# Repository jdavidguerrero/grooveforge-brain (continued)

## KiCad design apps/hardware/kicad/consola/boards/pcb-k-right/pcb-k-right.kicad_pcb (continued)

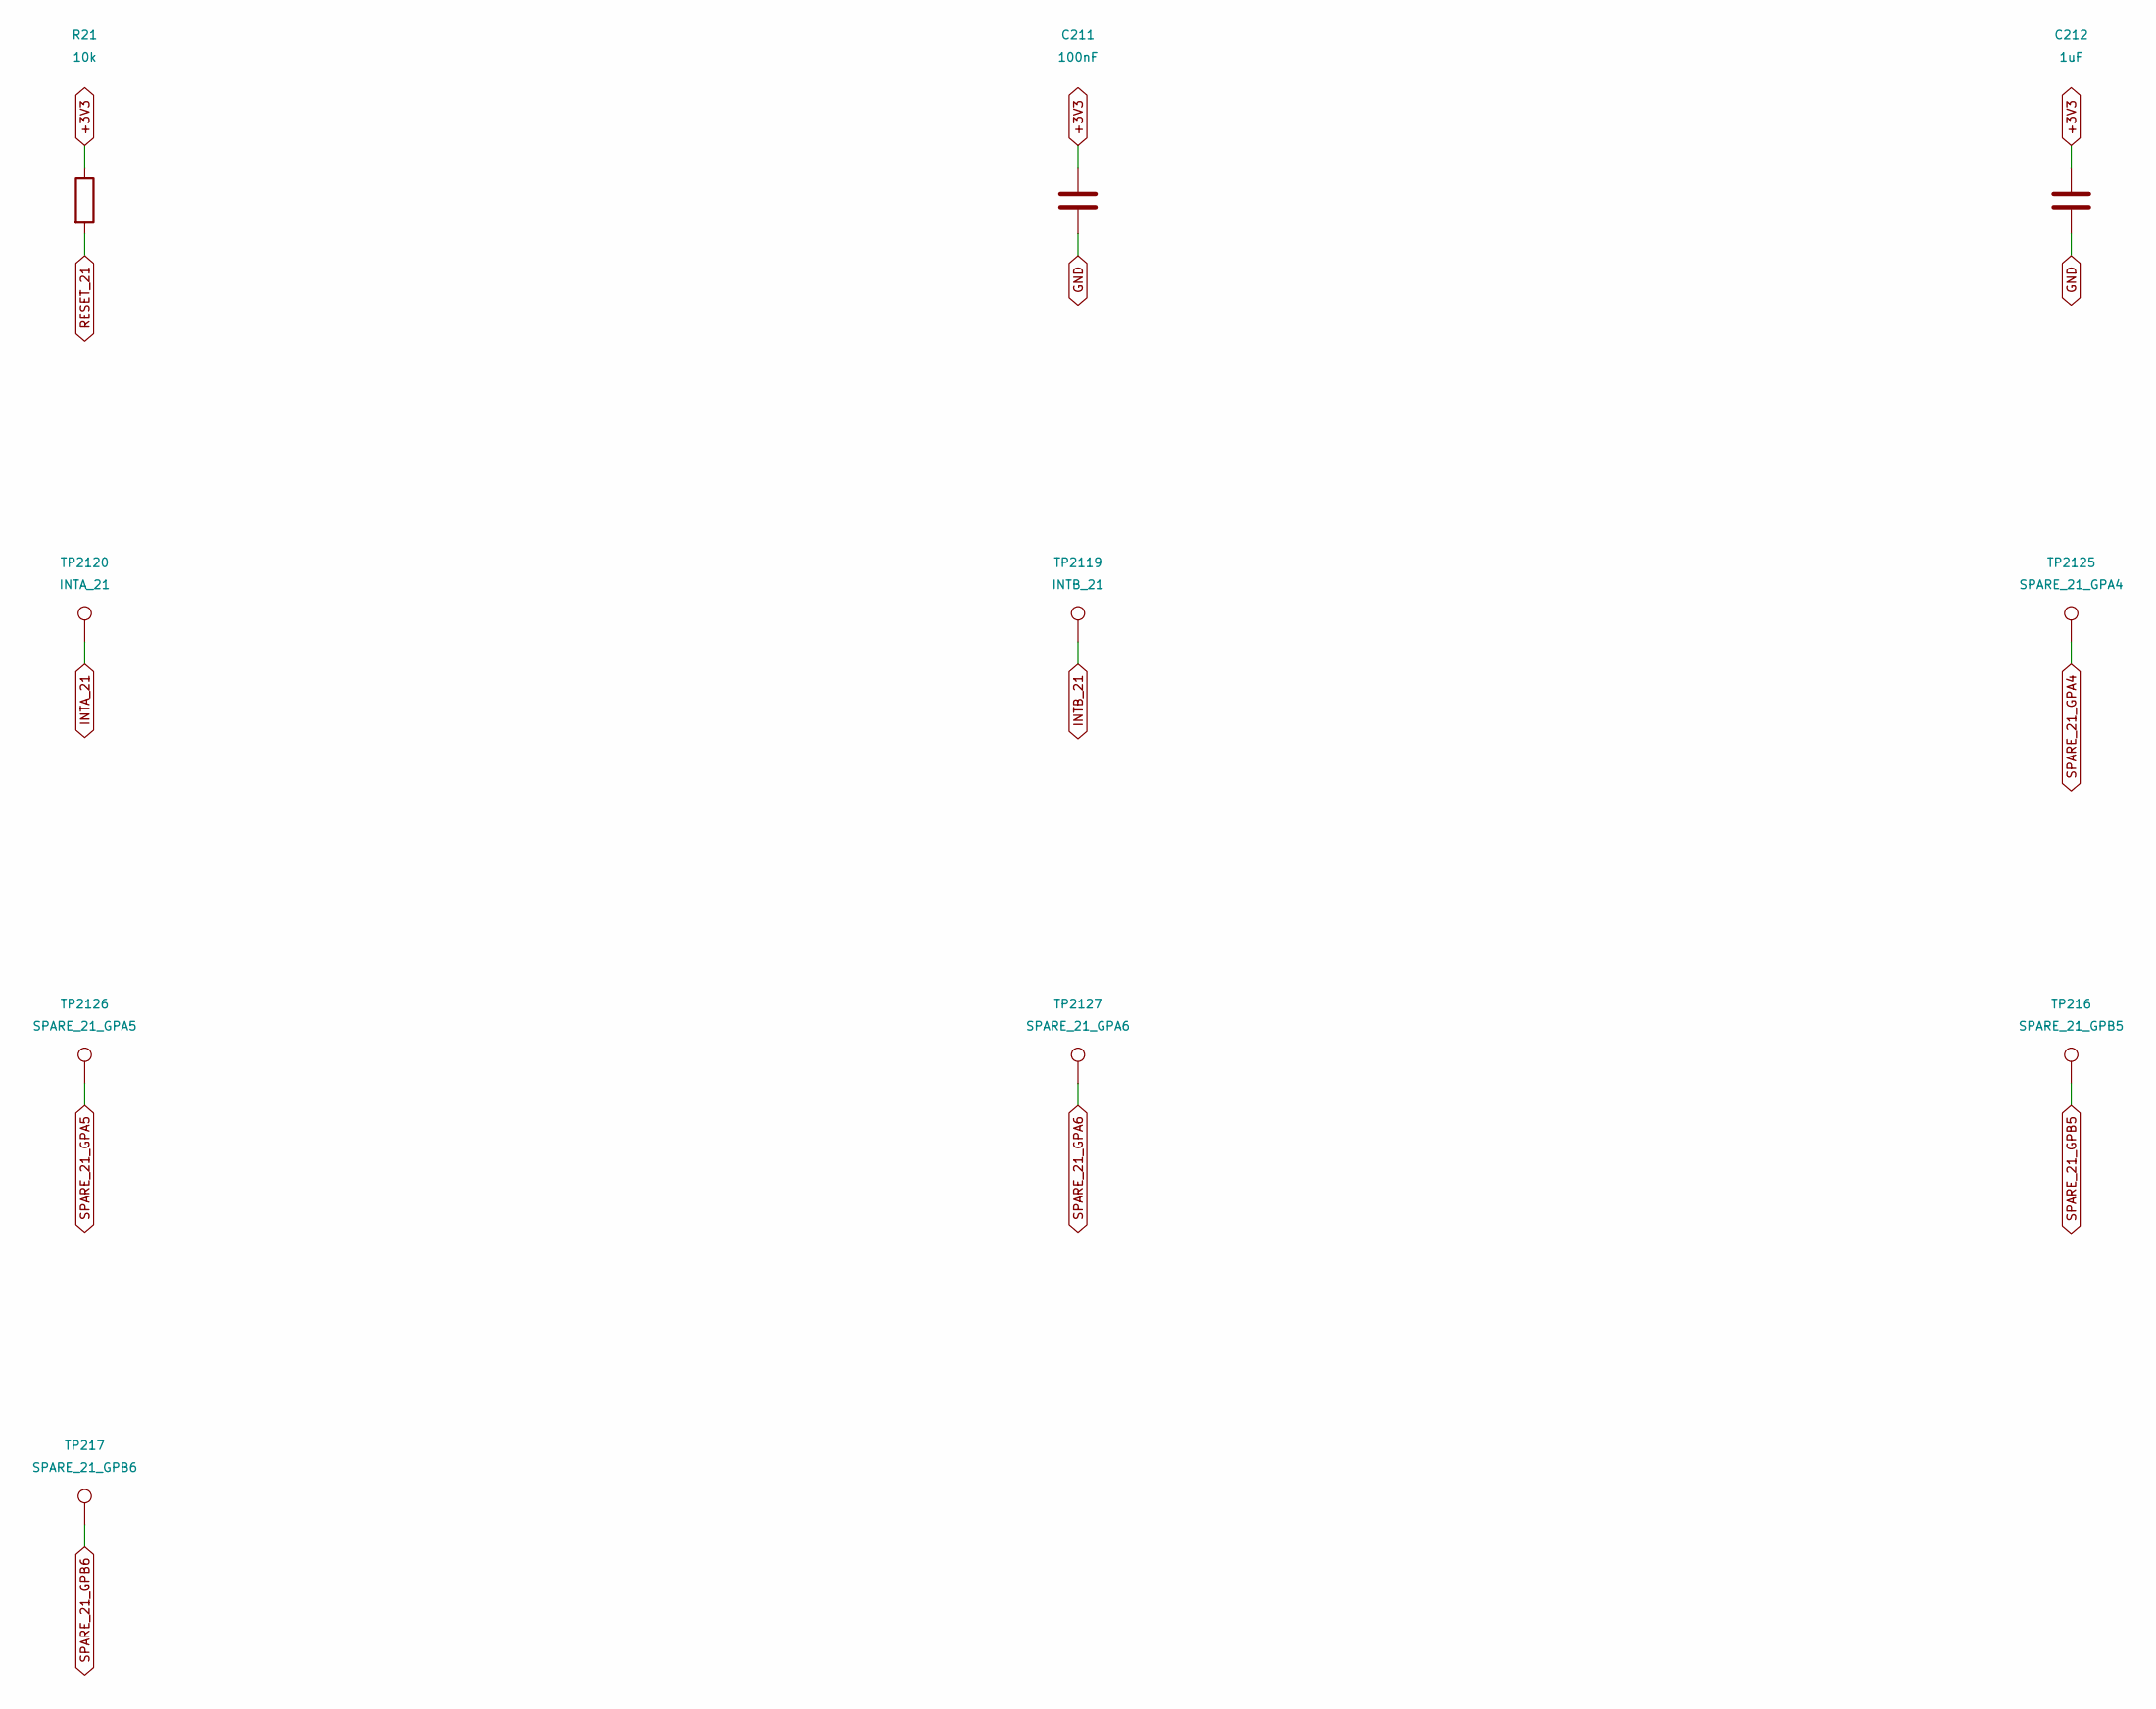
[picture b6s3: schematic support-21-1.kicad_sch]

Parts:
C211: 100nF; C_0805_2012Metric; MPN CC0805KRX7R9BB104; LCSC C49678
C212: 1uF; C_0805_2012Metric; MPN FCC0805B105K500FT; LCSC C5137478
R21: 10k; R_0805_2012Metric; MPN 0805W8F1002T5E; LCSC C17414
TP216: SPARE_21_GPB5; TestPoint_Pad_D1.5mm
TP217: SPARE_21_GPB6; TestPoint_Pad_D1.5mm
TP2119: INTB_21; TestPoint_Pad_D1.5mm
TP2120: INTA_21; TestPoint_Pad_D1.5mm
TP2125: SPARE_21_GPA4; TestPoint_Pad_D1.5mm
TP2126: SPARE_21_GPA5; TestPoint_Pad_D1.5mm
TP2127: SPARE_21_GPA6; TestPoint_Pad_D1.5mm

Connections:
+3V3: C211.1, C212.1, R21.1; also elsewhere on the board
GND: C211.2, C212.2; also elsewhere on the board
INTA_21: TP2120.1; also elsewhere on the board
INTB_21: TP2119.1; also elsewhere on the board
RESET_21: R21.2; also elsewhere on the board
SPARE_21_GPA4: TP2125.1; also elsewhere on the board
SPARE_21_GPA5: TP2126.1; also elsewhere on the board
SPARE_21_GPA6: TP2127.1; also elsewhere on the board
SPARE_21_GPB5: TP216.1; also elsewhere on the board
SPARE_21_GPB6: TP217.1; also elsewhere on the board

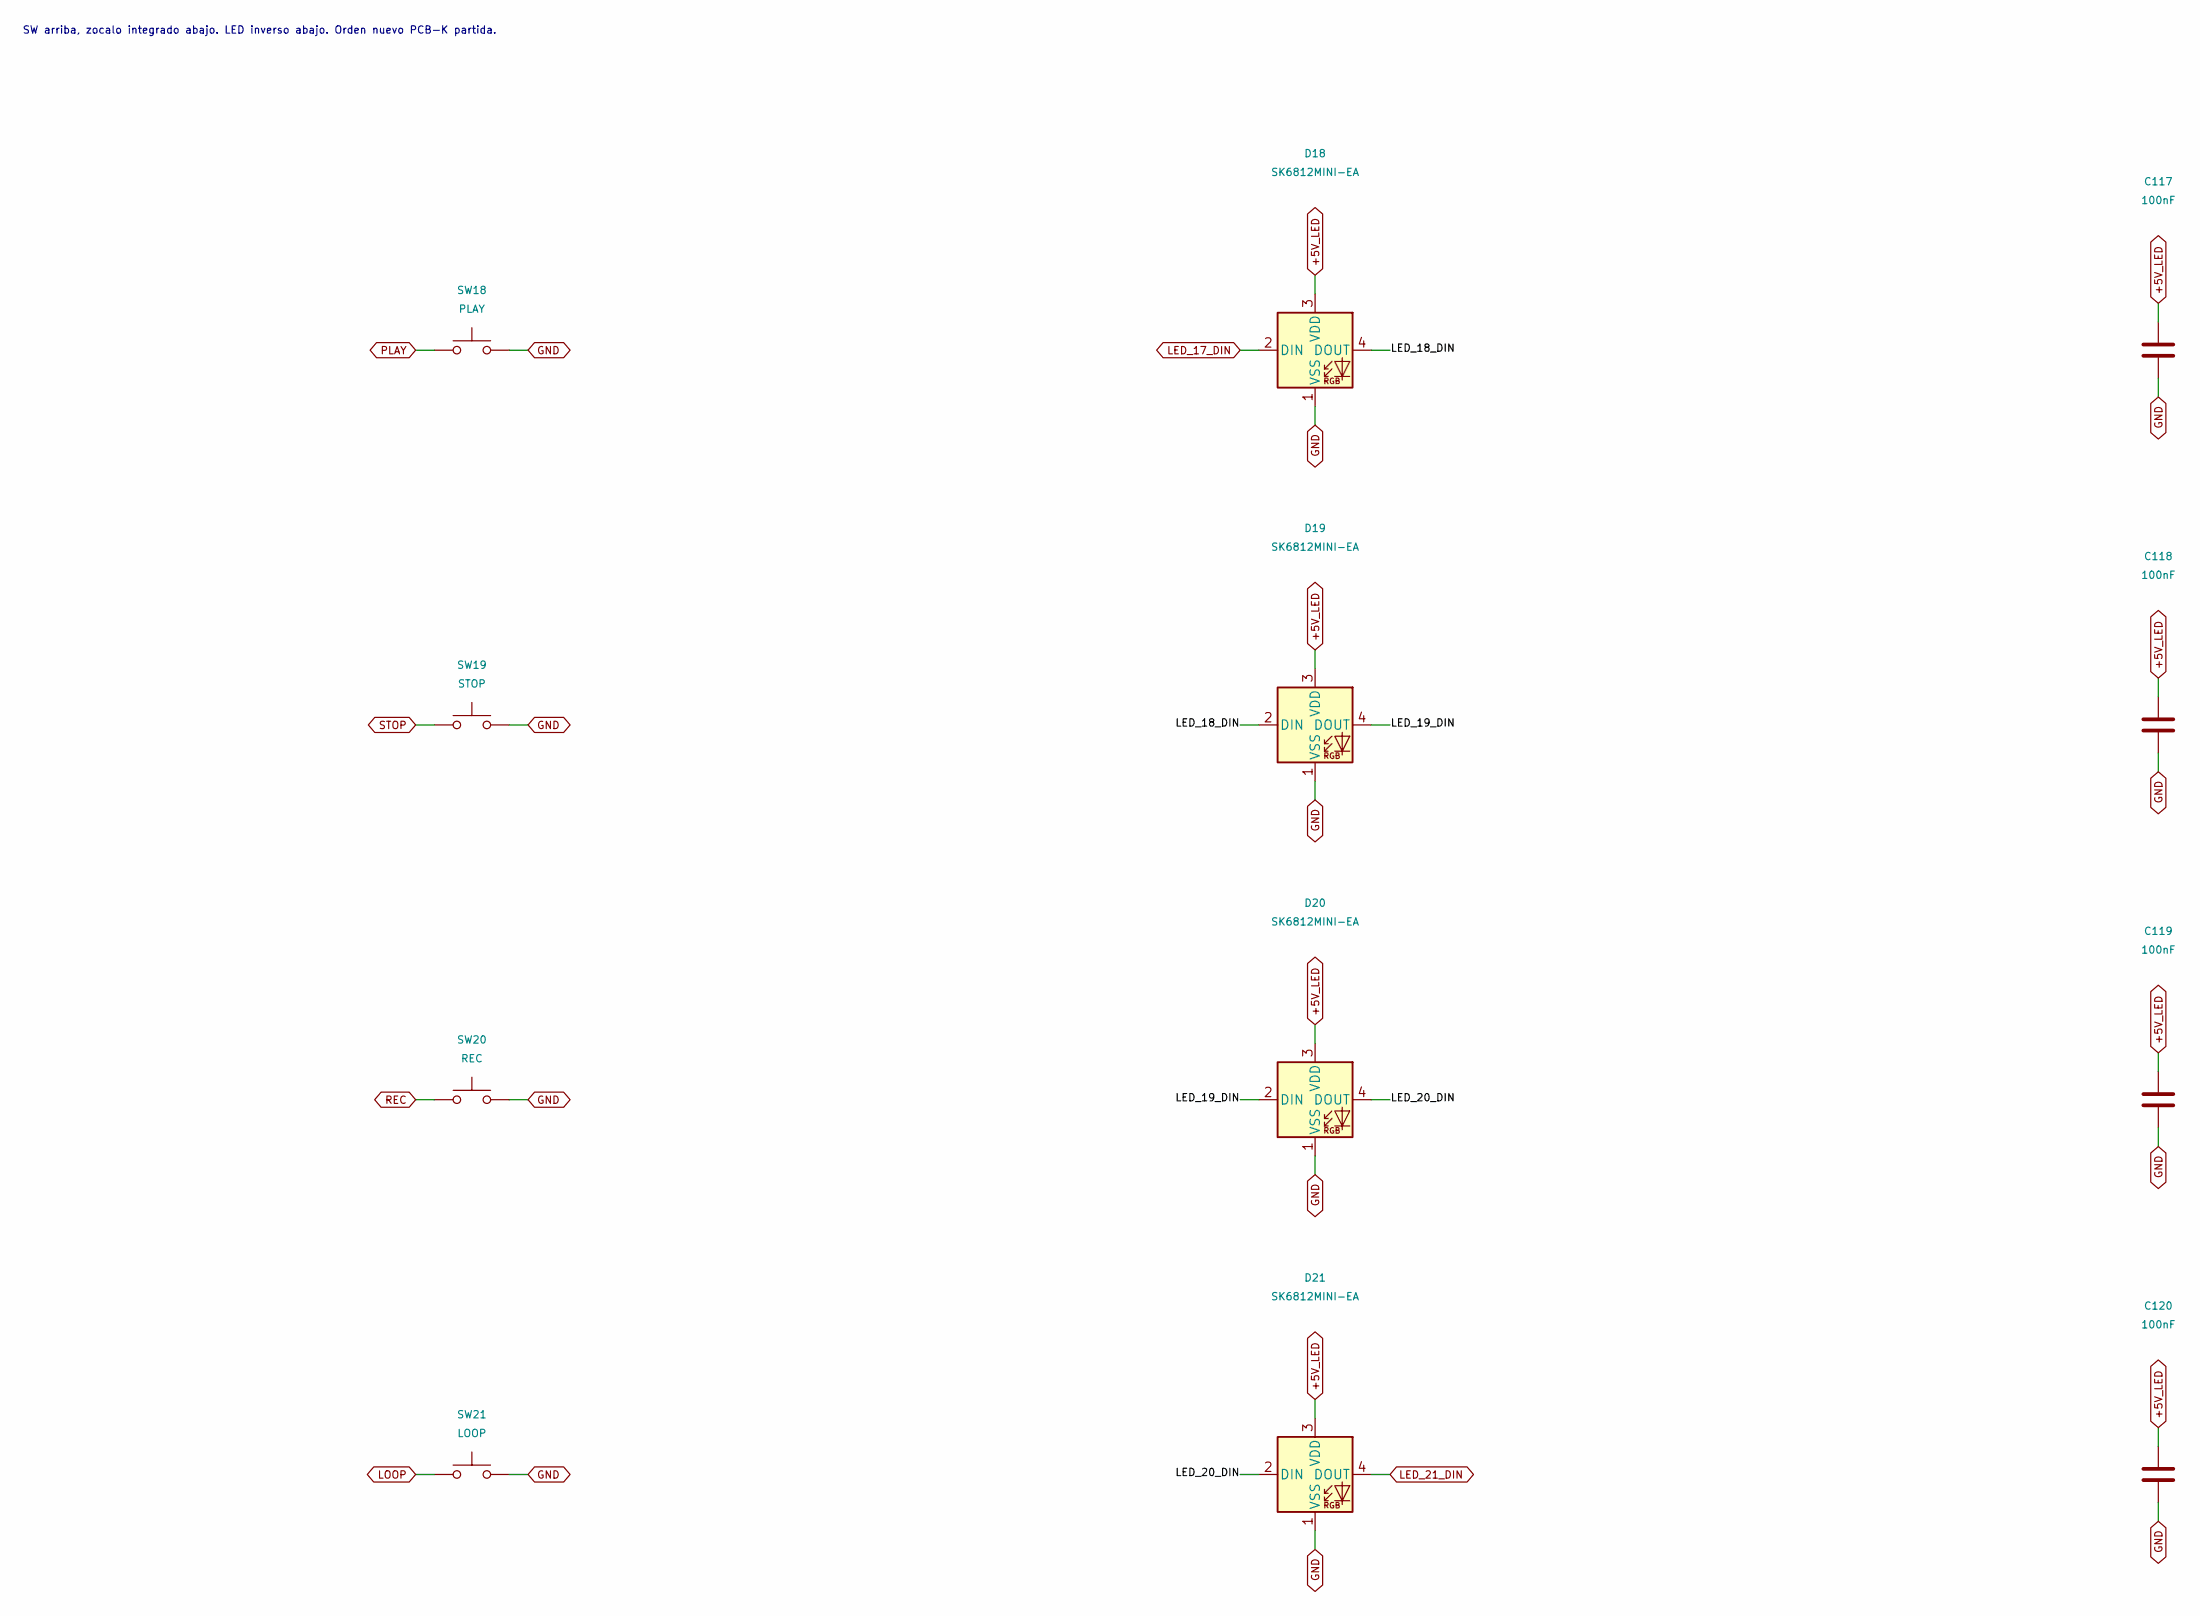
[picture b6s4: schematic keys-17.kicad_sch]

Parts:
C117, C118, C119, C120: 100nF; C_0805_2012Metric; MPN CC0805KRX7R9BB104; LCSC C49678
D18, D19, D20, D21: SK6812MINI-EA; SK6812MINI-EA_ReverseMount; MPN SK6812MINI-EA; LCSC C5378731
SW18: PLAY; Kailh_Choc_V2_PG1353_Hotswap
SW19: STOP; Kailh_Choc_V2_PG1353_Hotswap
SW20: REC; Kailh_Choc_V2_PG1353_Hotswap
SW21: LOOP; Kailh_Choc_V2_PG1353_Hotswap

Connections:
+5V_LED: C117.1, C118.1, C119.1, C120.1, D18.3 (VDD), D19.3 (VDD), D20.3 (VDD), D21.3 (VDD); also elsewhere on the board
/keys-17/LED_18_DIN: D18.4 (DOUT), D19.2 (DIN)
/keys-17/LED_19_DIN: D19.4 (DOUT), D20.2 (DIN)
/keys-17/LED_20_DIN: D20.4 (DOUT), D21.2 (DIN)
GND: C117.2, C118.2, C119.2, C120.2, D18.1 (VSS), D19.1 (VSS), D20.1 (VSS), D21.1 (VSS), SW18.2, SW19.2, SW20.2, SW21.2; also elsewhere on the board
LED_17_DIN: D18.2 (DIN); also elsewhere on the board
LED_21_DIN: D21.4 (DOUT); also elsewhere on the board
LOOP: SW21.1; also elsewhere on the board
PLAY: SW18.1; also elsewhere on the board
REC: SW20.1; also elsewhere on the board
STOP: SW19.1; also elsewhere on the board

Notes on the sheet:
SW arriba, zocalo integrado abajo. LED inverso abajo. Orden nuevo PCB-K partida.

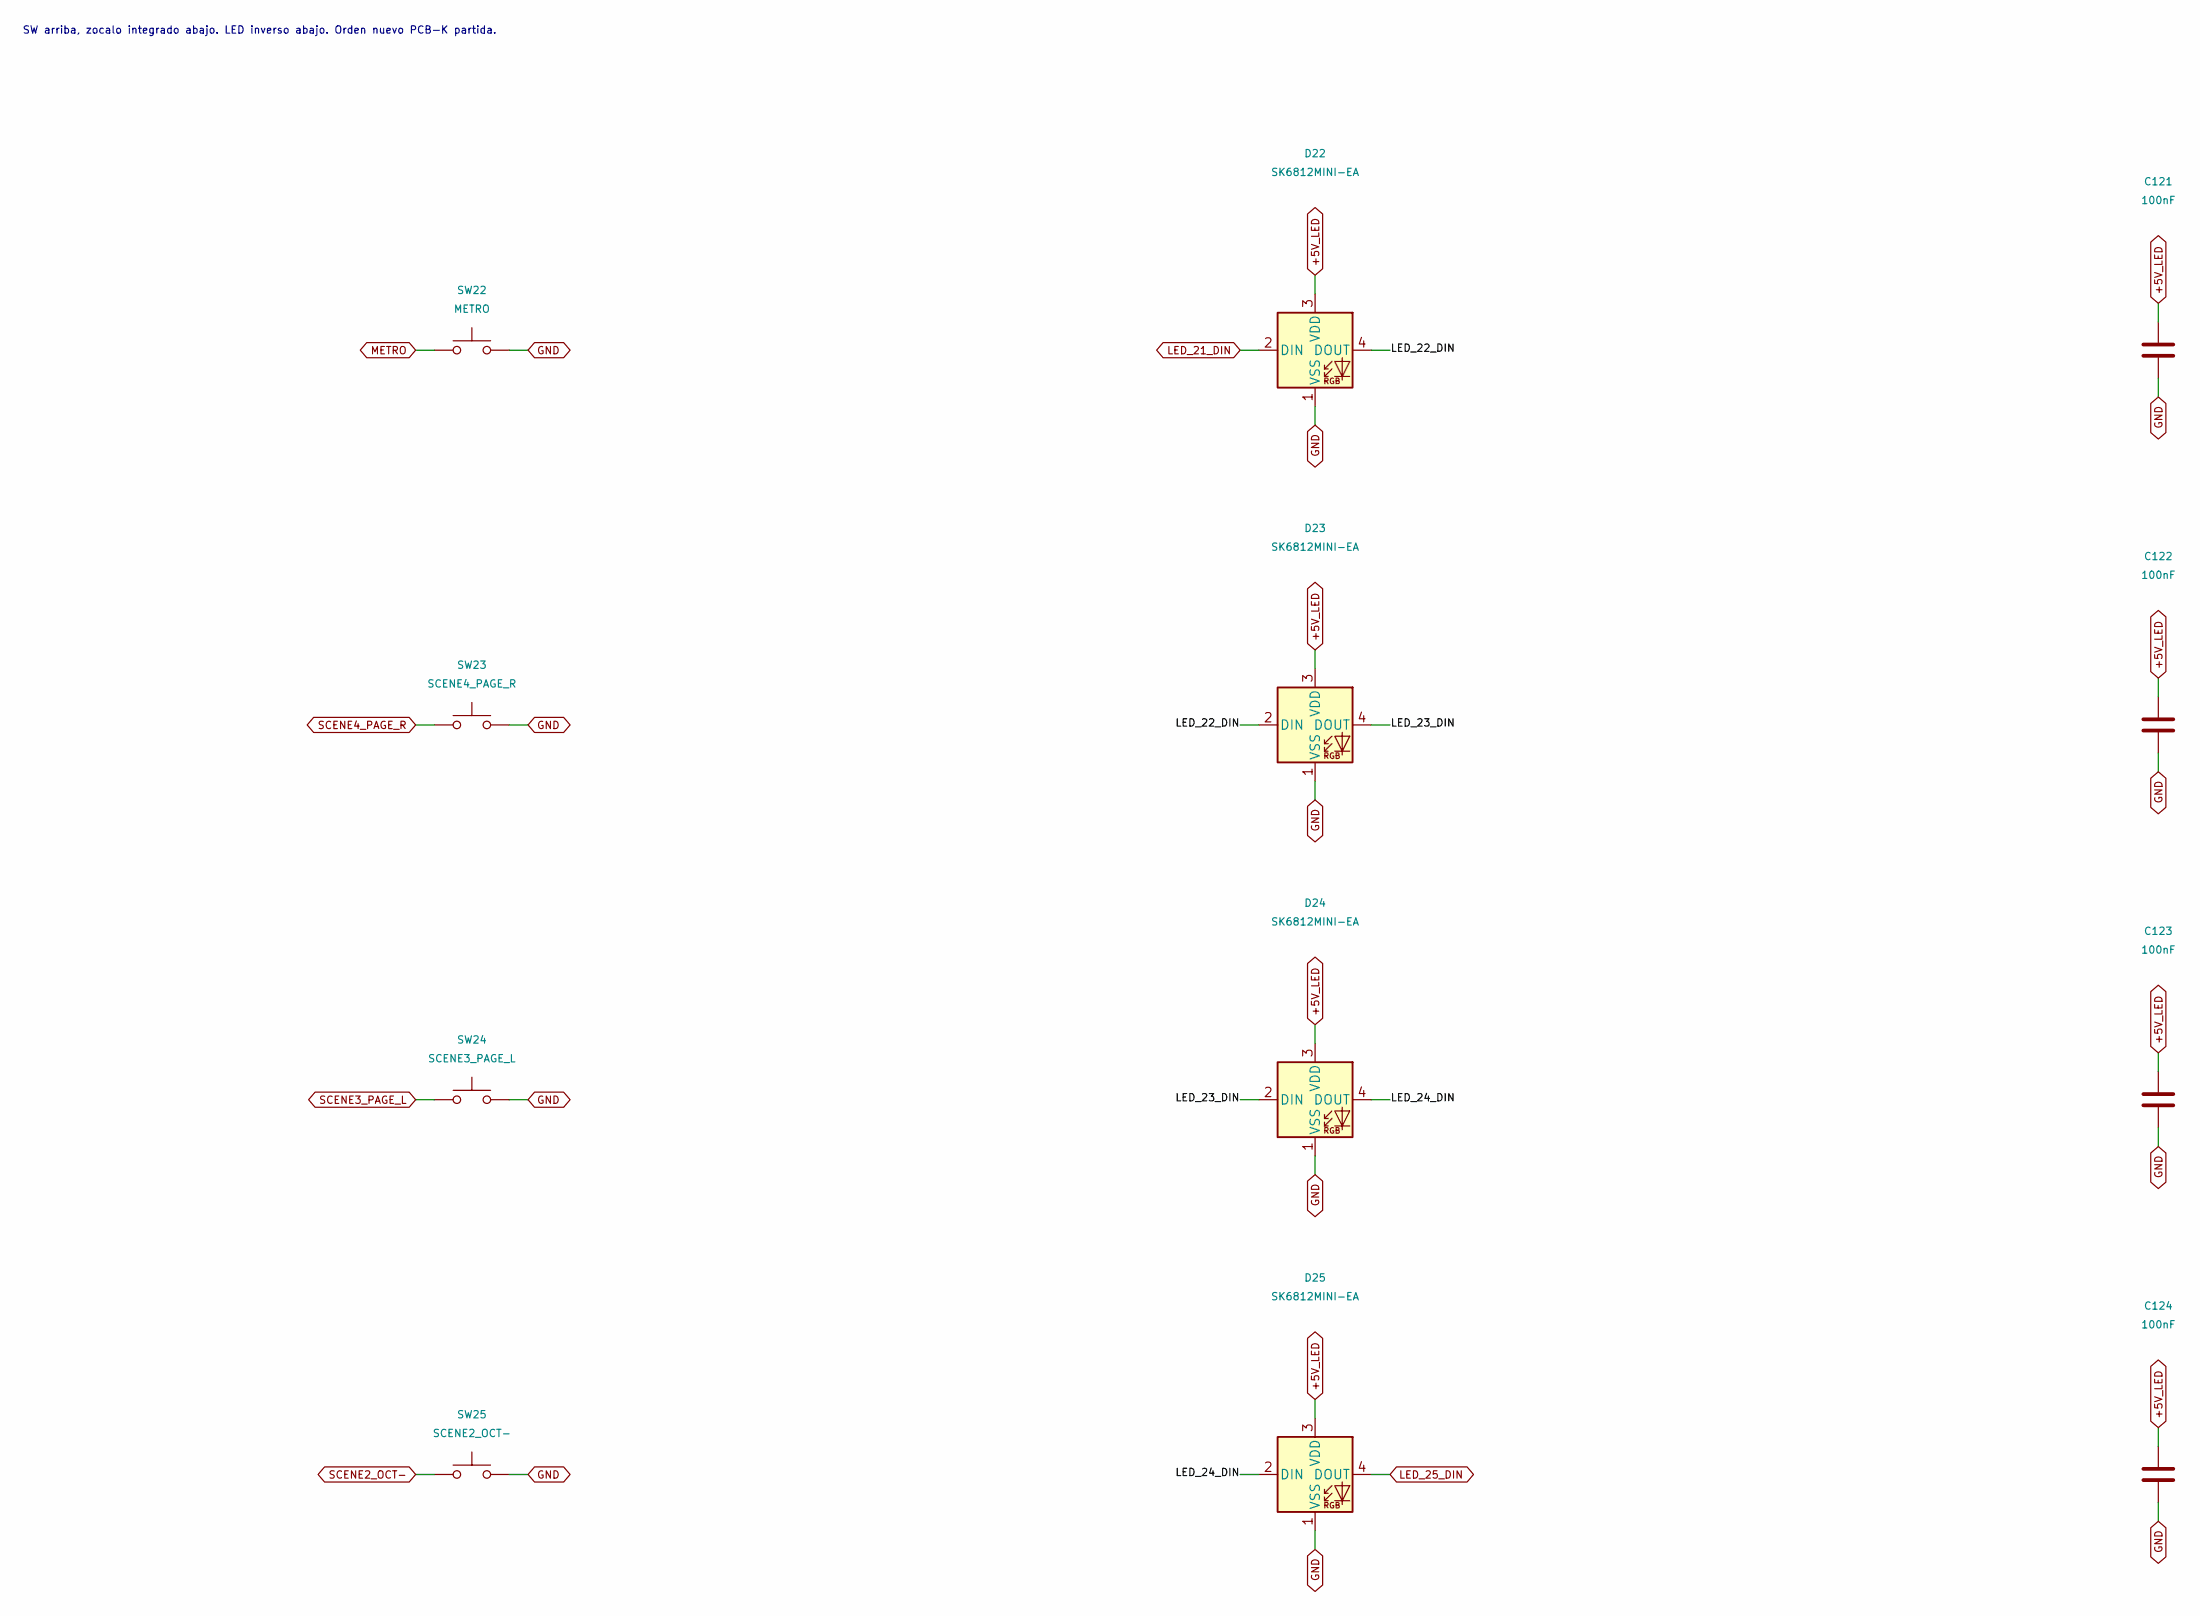
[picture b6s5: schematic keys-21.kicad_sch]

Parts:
C121, C122, C123, C124: 100nF; C_0805_2012Metric; MPN CC0805KRX7R9BB104; LCSC C49678
D22, D23, D24, D25: SK6812MINI-EA; SK6812MINI-EA_ReverseMount; MPN SK6812MINI-EA; LCSC C5378731
SW22: METRO; Kailh_Choc_V2_PG1353_Hotswap
SW23: SCENE4_PAGE_R; Kailh_Choc_V2_PG1353_Hotswap
SW24: SCENE3_PAGE_L; Kailh_Choc_V2_PG1353_Hotswap
SW25: SCENE2_OCT-; Kailh_Choc_V2_PG1353_Hotswap

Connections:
+5V_LED: C121.1, C122.1, C123.1, C124.1, D22.3 (VDD), D23.3 (VDD), D24.3 (VDD), D25.3 (VDD); also elsewhere on the board
/keys-21/LED_22_DIN: D22.4 (DOUT), D23.2 (DIN)
/keys-21/LED_23_DIN: D23.4 (DOUT), D24.2 (DIN)
/keys-21/LED_24_DIN: D24.4 (DOUT), D25.2 (DIN)
GND: C121.2, C122.2, C123.2, C124.2, D22.1 (VSS), D23.1 (VSS), D24.1 (VSS), D25.1 (VSS), SW22.2, SW23.2, SW24.2, SW25.2; also elsewhere on the board
LED_21_DIN: D22.2 (DIN); also elsewhere on the board
LED_25_DIN: D25.4 (DOUT); also elsewhere on the board
METRO: SW22.1; also elsewhere on the board
SCENE2_OCT-: SW25.1; also elsewhere on the board
SCENE3_PAGE_L: SW24.1; also elsewhere on the board
SCENE4_PAGE_R: SW23.1; also elsewhere on the board

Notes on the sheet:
SW arriba, zocalo integrado abajo. LED inverso abajo. Orden nuevo PCB-K partida.

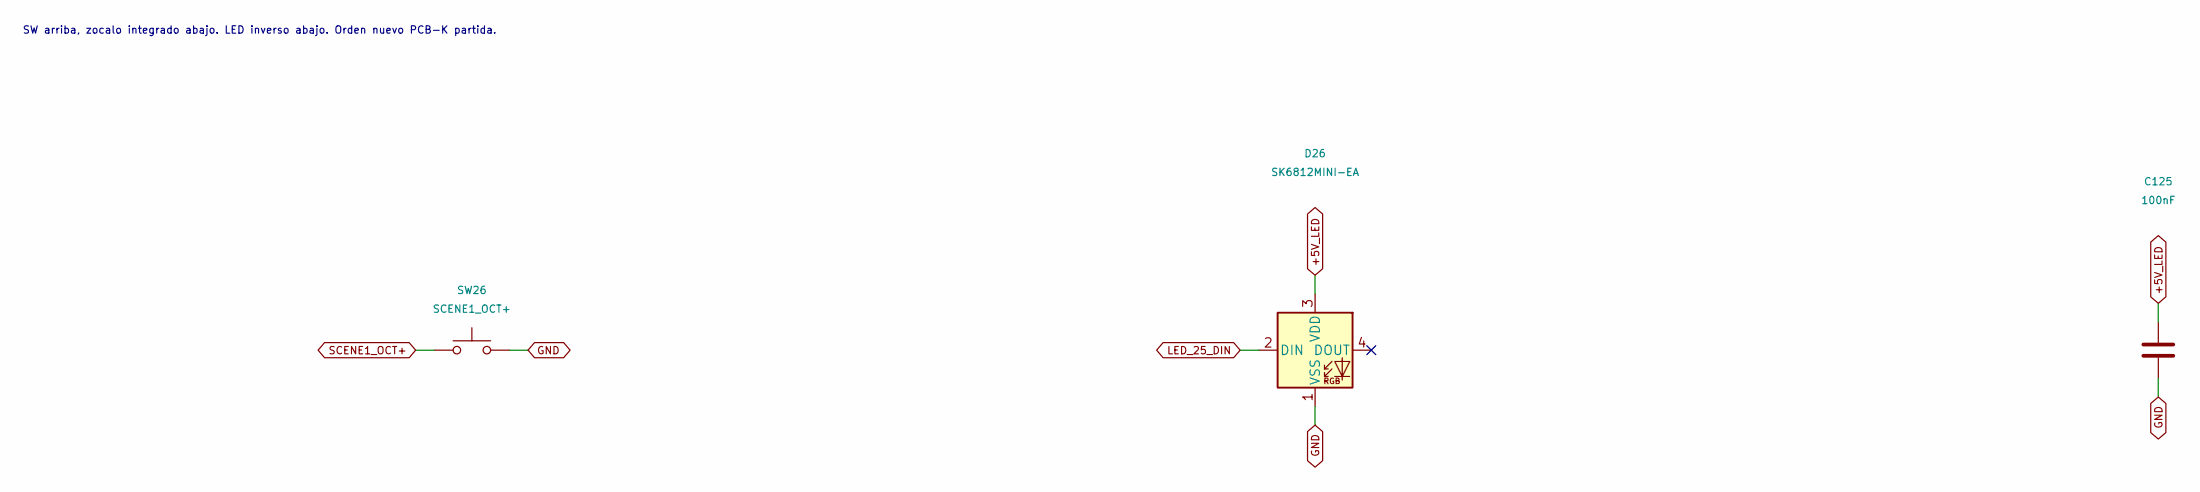
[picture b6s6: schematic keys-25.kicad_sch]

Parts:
C125: 100nF; C_0805_2012Metric; MPN CC0805KRX7R9BB104; LCSC C49678
D26: SK6812MINI-EA; SK6812MINI-EA_ReverseMount; MPN SK6812MINI-EA; LCSC C5378731
SW26: SCENE1_OCT+; Kailh_Choc_V2_PG1353_Hotswap

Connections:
+5V_LED: C125.1, D26.3 (VDD); also elsewhere on the board
GND: C125.2, D26.1 (VSS), SW26.2; also elsewhere on the board
LED_25_DIN: D26.2 (DIN); also elsewhere on the board
SCENE1_OCT+: SW26.1; also elsewhere on the board

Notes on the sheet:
SW arriba, zocalo integrado abajo. LED inverso abajo. Orden nuevo PCB-K partida.

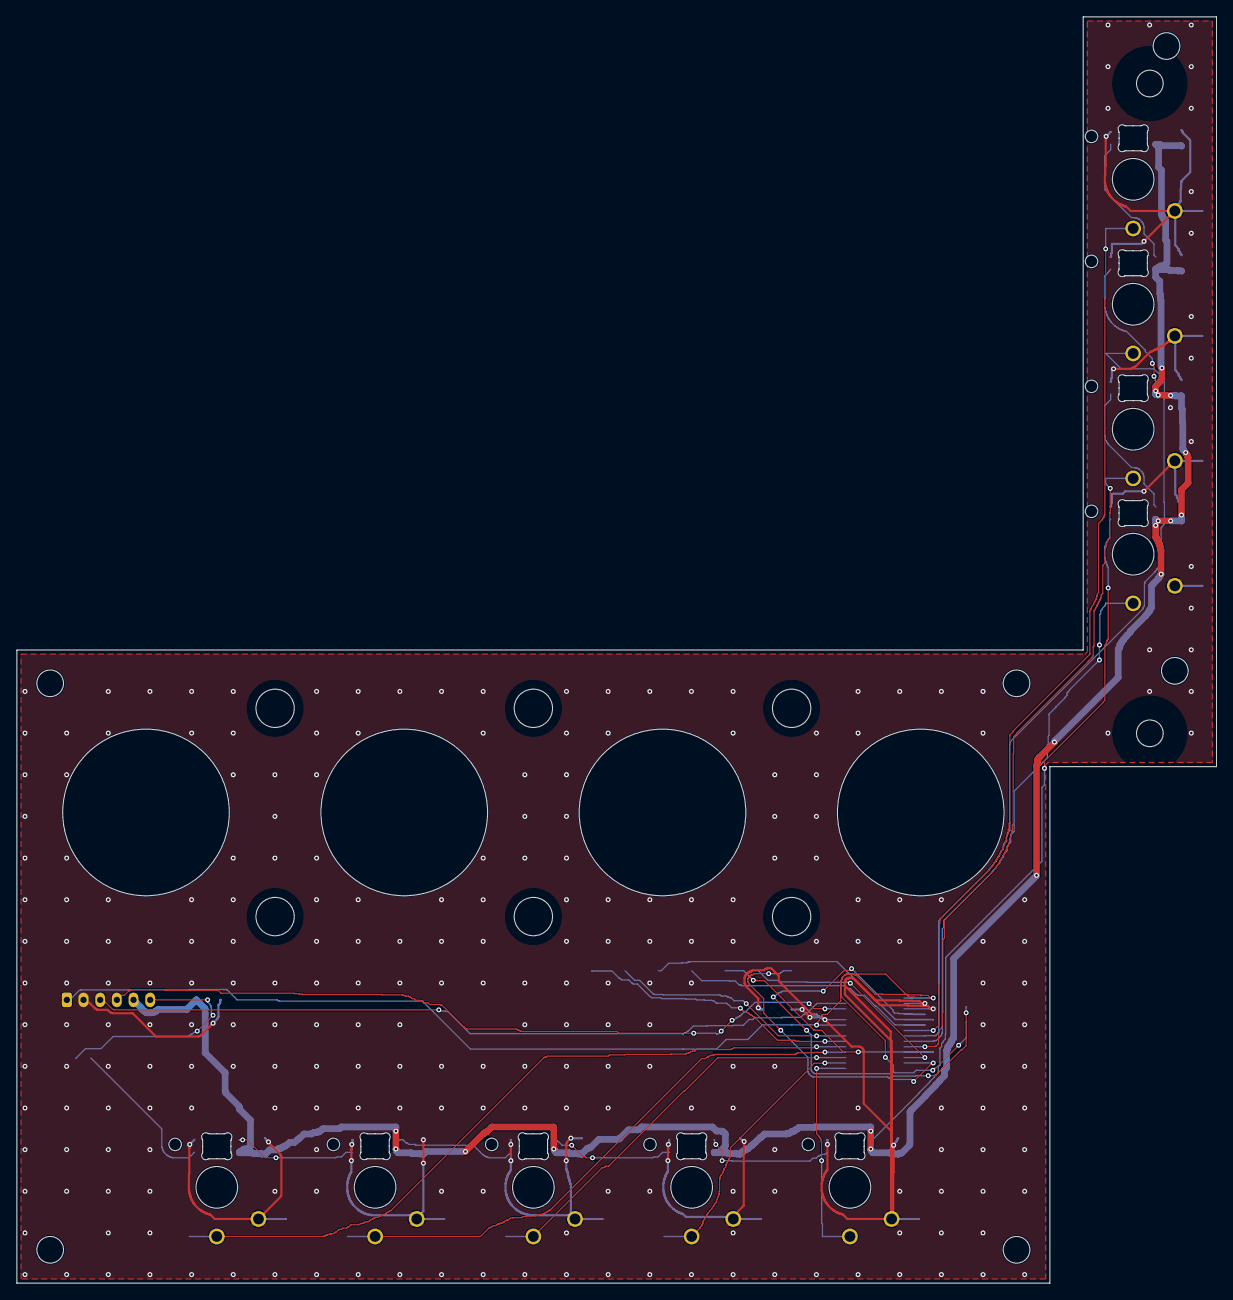
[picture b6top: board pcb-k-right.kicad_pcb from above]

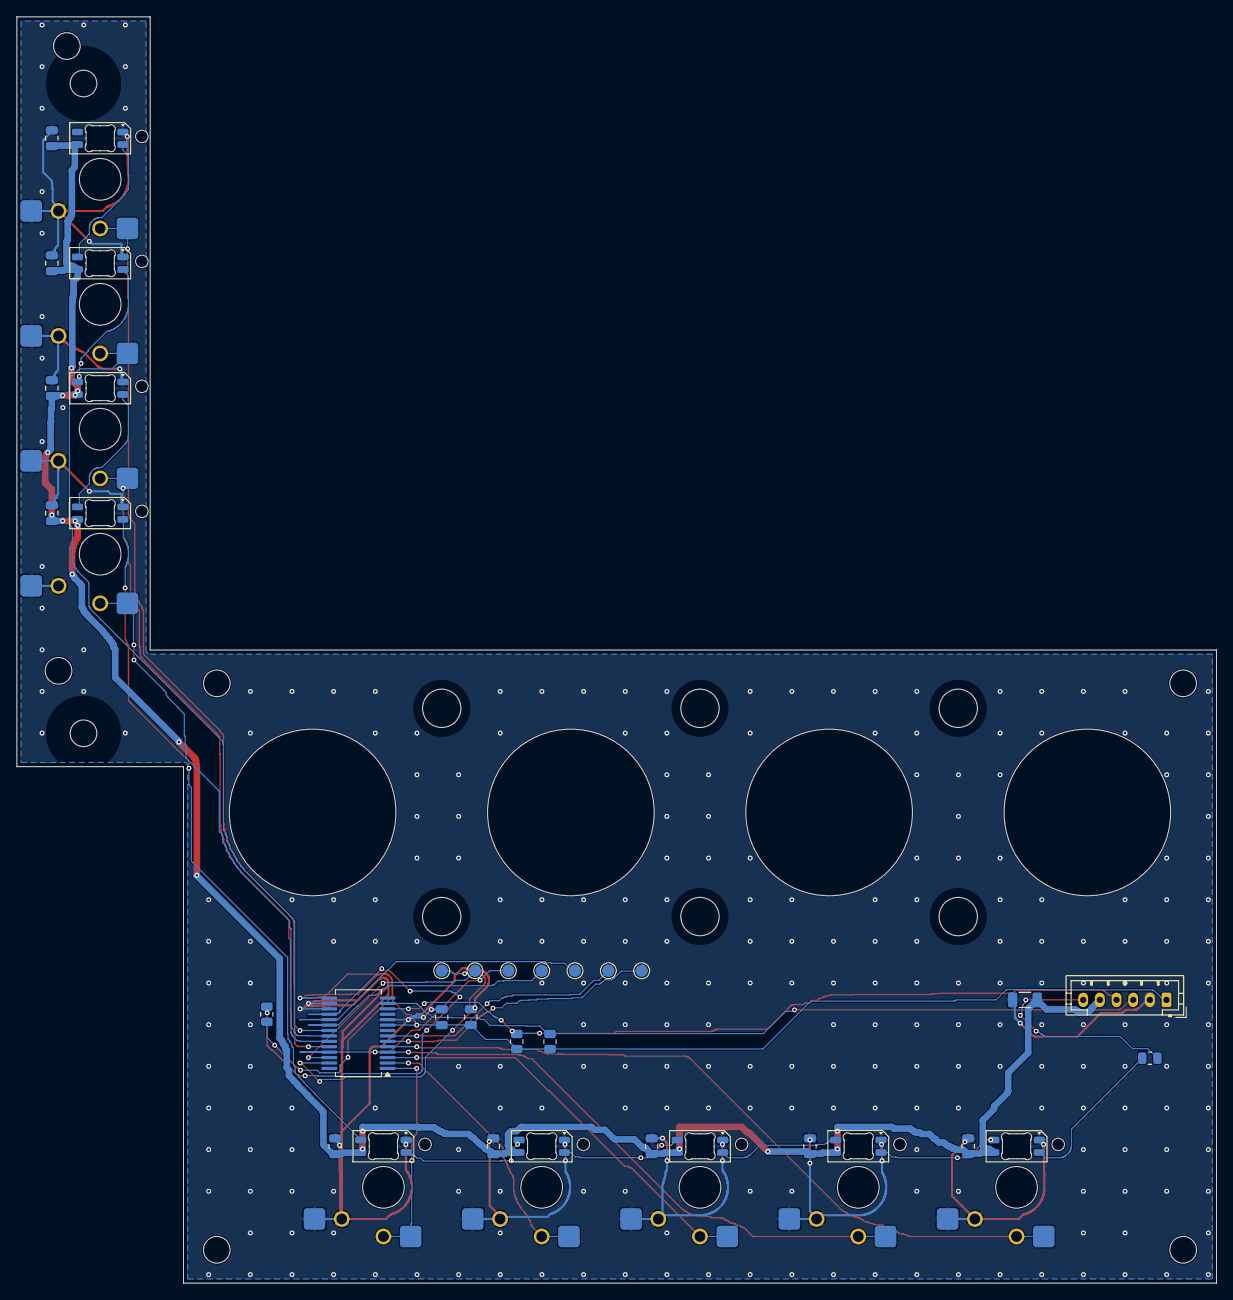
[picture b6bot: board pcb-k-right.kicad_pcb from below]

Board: 2 copper layers, 144.0 x 152.0 mm, 57 parts (34 on the bottom side), 32 nets.

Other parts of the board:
H1, H2, H3, H4, H5, H6, H7, H8: M2.5 PEM
H9, H10, H11, H12, H13, H14: PCB-P passthrough

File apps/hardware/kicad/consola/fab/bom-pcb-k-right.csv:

"Reference","Value","Footprint","LCSC","Supply","SupplyDescription","DNP"
"C1","22uF","Capacitor_SMD:C_1206_3216Metric","C12891","","",""
"C117","100nF","Capacitor_SMD:C_0805_2012Metric","C49678","","",""
"C118","100nF","Capacitor_SMD:C_0805_2012Metric","C49678","","",""
"C119","100nF","Capacitor_SMD:C_0805_2012Metric","C49678","","",""
"C120","100nF","Capacitor_SMD:C_0805_2012Metric","C49678","","",""
"C121","100nF","Capacitor_SMD:C_0805_2012Metric","C49678","","",""
"C122","100nF","Capacitor_SMD:C_0805_2012Metric","C49678","","",""
"C123","100nF","Capacitor_SMD:C_0805_2012Metric","C49678","","",""
"C124","100nF","Capacitor_SMD:C_0805_2012Metric","C49678","","",""
"C125","100nF","Capacitor_SMD:C_0805_2012Metric","C49678","","",""
"C211","100nF","Capacitor_SMD:C_0805_2012Metric","C49678","","",""
"C212","1uF","Capacitor_SMD:C_0805_2012Metric","C5137478","","",""
"D18","SK6812MINI-EA","gf_consola:SK6812MINI-EA_ReverseMount","C5378731","","",""
"D19","SK6812MINI-EA","gf_consola:SK6812MINI-EA_ReverseMount","C5378731","","",""
"D20","SK6812MINI-EA","gf_consola:SK6812MINI-EA_ReverseMount","C5378731","","",""
"D21","SK6812MINI-EA","gf_consola:SK6812MINI-EA_ReverseMount","C5378731","","",""
"D22","SK6812MINI-EA","gf_consola:SK6812MINI-EA_ReverseMount","C5378731","","",""
"D23","SK6812MINI-EA","gf_consola:SK6812MINI-EA_ReverseMount","C5378731","","",""
"D24","SK6812MINI-EA","gf_consola:SK6812MINI-EA_ReverseMount","C5378731","","",""
"D25","SK6812MINI-EA","gf_consola:SK6812MINI-EA_ReverseMount","C5378731","","",""
"D26","SK6812MINI-EA","gf_consola:SK6812MINI-EA_ReverseMount","C5378731","","",""
"J1","DESDE IZQUIERDA","Connector_JST:JST_PH_B6B-PH-K_1x06_P2.00mm_Vertical","C131342","","",""
"R1","33R","Resistor_SMD:R_0805_2012Metric","C17634","","",""
"R2","2.2k DNP","Resistor_SMD:R_0805_2012Metric","C17520","","","DNP"
"R3","2.2k DNP","Resistor_SMD:R_0805_2012Metric","C17520","","","DNP"
"R21","10k","Resistor_SMD:R_0805_2012Metric","C17414","","",""
"SW18","PLAY","gf_consola:Kailh_Choc_V2_PG1353_Hotswap","","owner","Juan: tecla Kailh Choc V2 PG1353 + zócalo Kailh CPG135001S30 comprado aparte por AliExpress",""
"SW19","STOP","gf_consola:Kailh_Choc_V2_PG1353_Hotswap","","owner","Juan: tecla Kailh Choc V2 PG1353 + zócalo Kailh CPG135001S30 comprado aparte por AliExpress",""
"SW20","REC","gf_consola:Kailh_Choc_V2_PG1353_Hotswap","","owner","Juan: tecla Kailh Choc V2 PG1353 + zócalo Kailh CPG135001S30 comprado aparte por AliExpress",""
"SW21","LOOP","gf_consola:Kailh_Choc_V2_PG1353_Hotswap","","owner","Juan: tecla Kailh Choc V2 PG1353 + zócalo Kailh CPG135001S30 comprado aparte por AliExpress",""
"SW22","METRO","gf_consola:Kailh_Choc_V2_PG1353_Hotswap","","owner","Juan: tecla Kailh Choc V2 PG1353 + zócalo Kailh CPG135001S30 comprado aparte por AliExpress",""
"SW23","SCENE4_PAGE_R","gf_consola:Kailh_Choc_V2_PG1353_Hotswap","","owner","Juan: tecla Kailh Choc V2 PG1353 + zócalo Kailh CPG135001S30 comprado aparte por AliExpress",""
"SW24","SCENE3_PAGE_L","gf_consola:Kailh_Choc_V2_PG1353_Hotswap","","owner","Juan: tecla Kailh Choc V2 PG1353 + zócalo Kailh CPG135001S30 comprado aparte por AliExpress",""
"SW25","SCENE2_OCT-","gf_consola:Kailh_Choc_V2_PG1353_Hotswap","","owner","Juan: tecla Kailh Choc V2 PG1353 + zócalo Kailh CPG135001S30 comprado aparte por AliExpress",""
"SW26","SCENE1_OCT+","gf_consola:Kailh_Choc_V2_PG1353_Hotswap","","owner","Juan: tecla Kailh Choc V2 PG1353 + zócalo Kailh CPG135001S30 comprado aparte por AliExpress",""
"TP216","SPARE_21_GPB5","TestPoint:TestPoint_Pad_D1.5mm","","","",""
"TP217","SPARE_21_GPB6","TestPoint:TestPoint_Pad_D1.5mm","","","",""
"TP2119","INTB_21","TestPoint:TestPoint_Pad_D1.5mm","","","",""
"TP2120","INTA_21","TestPoint:TestPoint_Pad_D1.5mm","","","",""
"TP2125","SPARE_21_GPA4","TestPoint:TestPoint_Pad_D1.5mm","","","",""
"TP2126","SPARE_21_GPA5","TestPoint:TestPoint_Pad_D1.5mm","","","",""
"TP2127","SPARE_21_GPA6","TestPoint:TestPoint_Pad_D1.5mm","","","",""
"U21","MCP23017-E/SS 0x21","Package_SO:SSOP-28_5.3x10.2mm_P0.65mm","C506653","","",""
